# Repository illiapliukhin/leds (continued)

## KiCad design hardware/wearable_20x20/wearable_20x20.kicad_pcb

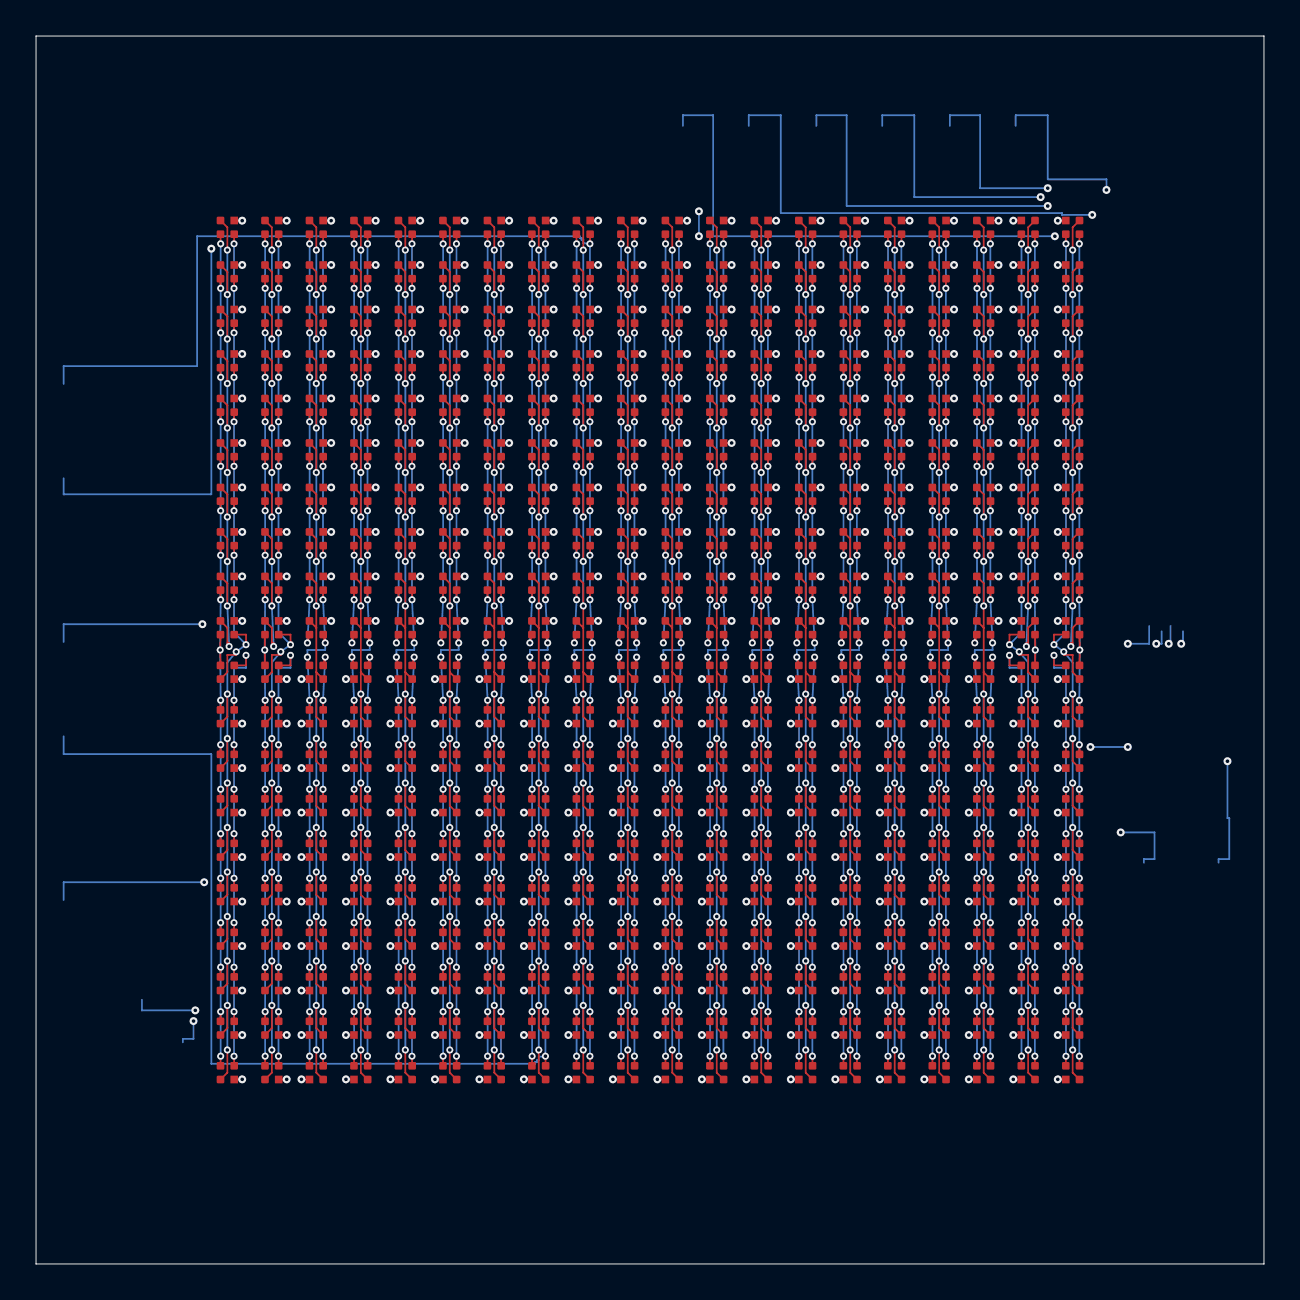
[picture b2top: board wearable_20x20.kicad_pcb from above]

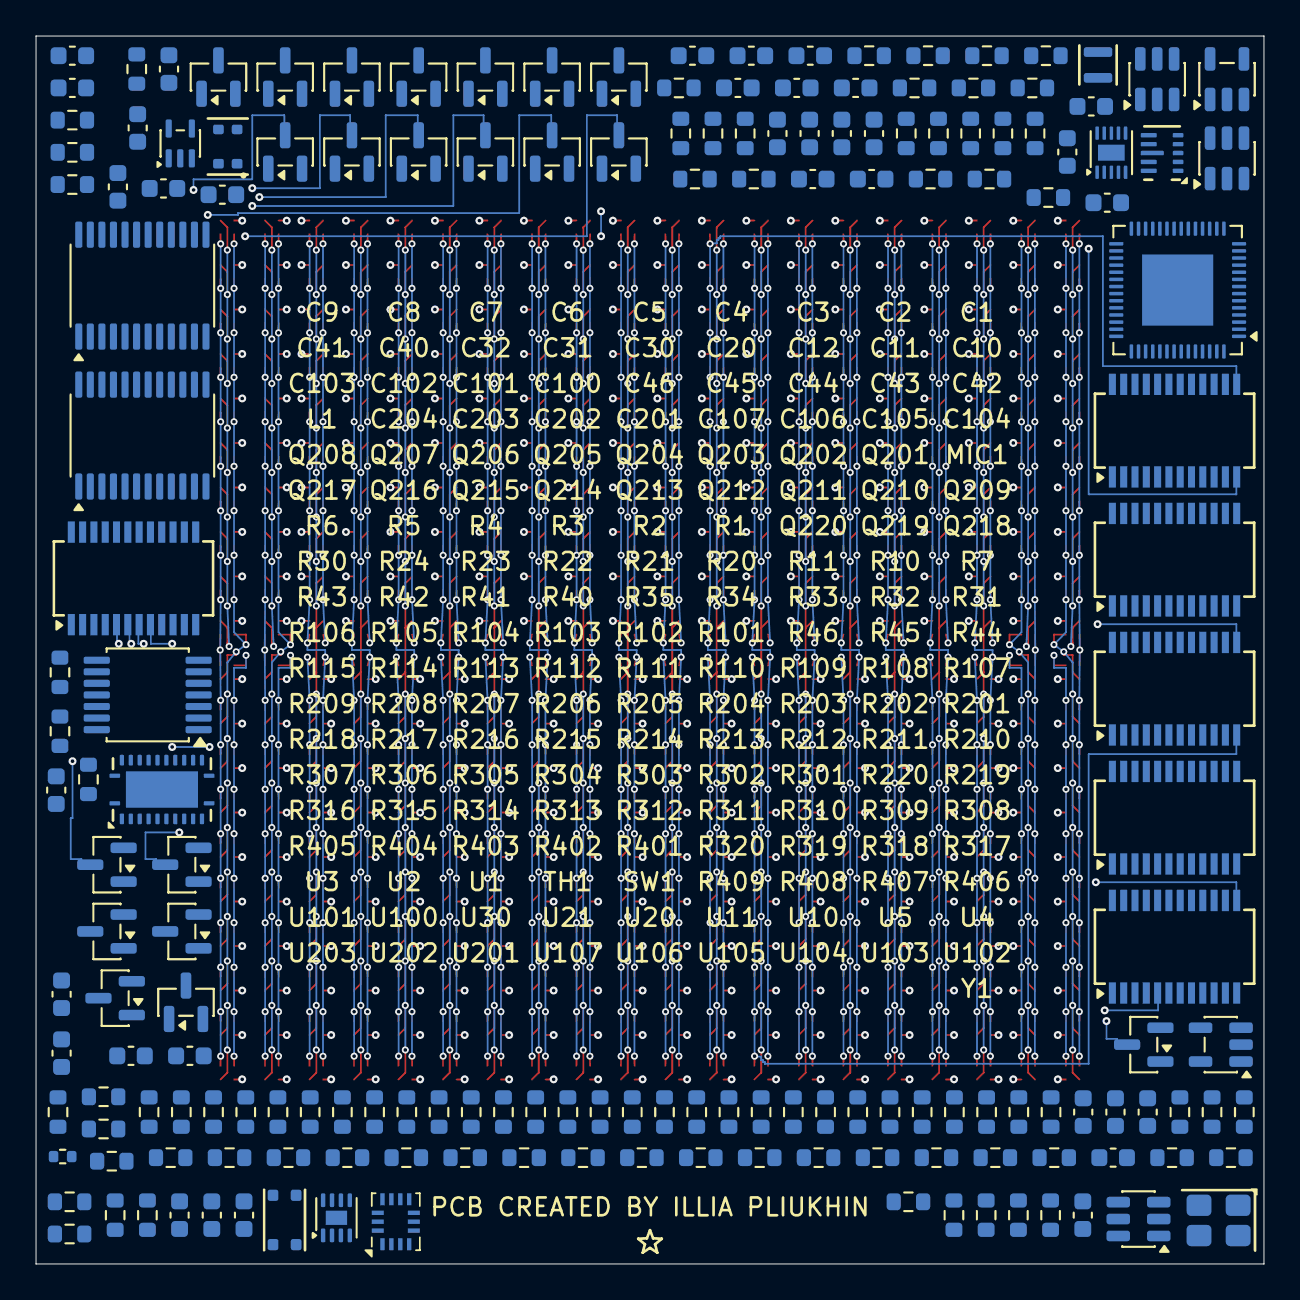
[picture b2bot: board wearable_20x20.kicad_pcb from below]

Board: 4 copper layers, 69.0 x 69.0 mm, 572 parts (172 on the bottom side), 205 nets.

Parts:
C1, C3, C4, C20, C40, C42: 1uF; C_0603_1608Metric
C2, C6, C10, C12: 10uF; C_0603_1608Metric
C5: 4.7uF; C_0603_1608Metric
C7, C8: 22uF; C_0603_1608Metric
C9, C11: 1nF; C_0603_1608Metric
C30, C32, C41, C43, C46, C100, C101, C102, C103, C104, C105, C106, C107, C201, C202, C203, C204: 100nF; C_0603_1608Metric
C31: 2.2uF; C_0603_1608Metric
C44: 100pF; C_0603_1608Metric
C45: 22nF; C_0603_1608Metric
D1, D2, D3, D4, D5, D6, D7, D8, D9, D10, D11, D12, D13, D14, D15, D16, D17, D18, D19, D20, D21, D22, D23, D24, D25, D26, D27, D28, D29, D30, D31, D32, D33, D34, D35, D36, D37, D38, D39, D40, D41, D42, D43, D44, D45, D46, D47, D48, D49, D50, D51, D52, D53, D54, D55, D56, D57, D58, D59, D60, D61, D62, D63, D64, D65, D66, D67, D68, D69, D70, D71, D72, D73, D74, D75, D76, D77, D78, D79, D80, D81, D82, D83, D84, D85, D86, D87, D88, D89, D90, D91, D92, D93, D94, D95, D96, D97, D98, D99, D100, D101, D102, D103, D104, D105, D106, D107, D108, D109, D110, D111, D112, D113, D114, D115, D116, D117, D118, D119, D120, D121, D122, D123, D124, D125, D126, D127, D128, D129, D130, D131, D132, D133, D134, D135, D136, D137, D138, D139, D140, D141, D142, D143, D144, D145, D146, D147, D148, D149, D150, D151, D152, D153, D154, D155, D156, D157, D158, D159, D160, D161, D162, D163, D164, D165, D166, D167, D168, D169, D170, D171, D172, D173, D174, D175, D176, D177, D178, D179, D180, D181, D182, D183, D184, D185, D186, D187, D188, D189, D190, D191, D192, D193, D194, D195, D196, D197, D198, D199, D200, D201, D202, D203, D204, D205, D206, D207, D208, D209, D210, D211, D212, D213, D214, D215, D216, D217, D218, D219, D220, D221, D222, D223, D224, D225, D226, D227, D228, D229, D230, D231, D232, D233, D234, D235, D236, D237, D238, D239, D240, D241, D242, D243, D244, D245, D246, D247, D248, D249, D250, D251, D252, D253, D254, D255, D256, D257, D258, D259, D260, D261, D262, D263, D264, D265, D266, D267, D268, D269, D270, D271, D272, D273, D274, D275, D276, D277, D278, D279, D280, D281, D282, D283, D284, D285, D286, D287, D288, D289, D290, D291, D292, D293, D294, D295, D296, D297, D298, D299, D300, D301, D302, D303, D304, D305, D306, D307, D308, D309, D310, D311, D312, D313, D314, D315, D316, D317, D318, D319, D320, D321, D322, D323, D324, D325, D326, D327, D328, D329, D330, D331, D332, D333, D334, D335, D336, D337, D338, D339, D340, D341, D342, D343, D344, D345, D346, D347, D348, D349, D350, D351, D352, D353, D354, D355, D356, D357, D358, D359, D360, D361, D362, D363, D364, D365, D366, D367, D368, D369, D370, D371, D372, D373, D374, D375, D376, D377, D378, D379, D380, D381, D382, D383, D384, D385, D386, D387, D388, D389, D390, D391, D392, D393, D394, D395, D396, D397, D398, D399, D400: MHPA1010RGBDT
L1: DFE201612E-R47M=P2 0.47uH; Murata_DFE201612E_2.0x1.6mm
MIC1: NA-FFA381-A10-1; Gettop_NA-FFA381-A10-1_TopPort_Microphone
Q201, Q202, Q203, Q204, Q205, Q206, Q207, Q208, Q209, Q210, Q211, Q212, Q213, Q214, Q215, Q216, Q217, Q218, Q219, Q220: AO3403; SOT-23
R1: 24k; R_0603_1608Metric
R2, R7, R45: 1k; R_0603_1608Metric
R3: 655k 0.1%; R_0603_1608Metric
R4: 91k 0.1%; R_0603_1608Metric
R5, R6, R10, R32, R46, R107, R108, R109, R110, R402, R403, R404, R405: 100k; R_0603_1608Metric
R11: DNP; R_0603_1608Metric
R20, R33, R43, R401: 10k; R_0603_1608Metric
R21, R22, R113, R114, R115: 22R; R_0603_1608Metric
R23, R24: 5.1k; R_0603_1608Metric
R30, R31: 4.7k; R_0603_1608Metric
R34, R35, R408, R409: 0R; R_0603_1608Metric
R40: 100R; R_0603_1608Metric
R41, R42, R111, R112, R301, R302, R303, R304, R305, R306, R307, R308, R309, R310, R311, R312, R313, R314, R315, R316, R317, R318, R319, R320, R406, R407: 47k; R_0603_1608Metric
R44: 200k; R_0603_1608Metric
R101, R102, R103, R104, R105, R106: 1.96k 0.1%; R_0603_1608Metric
R201, R202, R203, R204, R205, R206, R207, R208, R209, R210, R211, R212, R213, R214, R215, R216, R217, R218, R219, R220: 33R; R_0603_1608Metric
SW1: EVPBL2A1F000; Panasonic_EVPBL2A1F000_Switch
TH1: TE 20021086-05 10k 1% B3435; R_0402_1005Metric
U1: BQ25185; Texas_DLH0010A_WSON-10-1EP_2.2x2mm_P0.4mm_EP0.9x1.5mm
U2: TPS7A2033PDBVR; SOT-23-5
U3: TPS63802DLAR; TI_DLA0010A_VSON-HR-10_2x3mm_P0.5mm
U4, U5: TPS22917DBVR; SOT-23-6
U10: ESP32-S3FN8; QFN-56-1EP_7x7mm_P0.4mm_EP4x4mm
U11: USBLC6-2SC6; SOT-23-6
U20: BMI270; Bosch_LGA-14_3x2.5mm_P0.5mm
U21: MAX17048G+T10; TDFN-8-1EP_2x2mm_P0.5mm_EP0.8x1.2mm
U30: TLV9001IDCKR; SOT-353_SC-70-5
U100: SN74LV125APWR; TSSOP-14_4.4x5mm_P0.65mm
U101, U102, U103, U104, U105, U106: MBI5124GP-B; SSOP-24_3.9x8.7mm_P0.635mm
U107: SN74LVC1G125DBVR; SOT-23-5
U201: SN74LVC8T245RHLR; TI_RHL0024A_VQFN-24-1EP_3.5x5.5mm_P0.5mm_EP2.05x4.05mm
U202, U203: 74HC154PW,118; TSSOP-24_4.4x7.8mm_P0.65mm
Y1: L327S400H11L 40MHz 10pF; Lucki_L327S400H11L_Crystal_3225-4Pin

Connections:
AON_3V3: C5.1, C30.1, C31.1, C201.1, R20.1, R30.1, R31.1, R32.2, R111.1, R401.2, U2.5, U4.1, U5.1, U10.2, U10.3, U10.20, U10.46, U10.55, U10.56, U20.5, U20.8, U20.10, U20.12, U201.1, U201.2
AUDIO_3V3: C12.1, C46.1, R40.2, R41.2, U5.6, U30.5
AUDIO_3V3_CT: C11.1, U5.4
AUDIO_3V3_QOD: R11.2, U5.5
AUDIO_EN: R10.2, U5.3, U10.42
BAT_RAW: C3.1, C32.1, U1.2, U21.2, U21.3
BMI_ASCX_UNUSED: R35.2, U20.3
BMI_ASDX_UNUSED: R34.2, U20.2
BUTTON_WAKE_N: R32.1, SW1.1, U10.16
CHG_CE_N: U1.4, U10.43
CHG_ILIM_SET: R1.2, U1.7
CHG_ISET: R2.2, U1.8
CHG_STAT1_N: U1.9, U10.44
CHG_STAT2_N: U1.3, U10.45
CHIP_PU: C20.1, R20.2, U10.4
COL_B_01: D1.4 (K_B), D21.4 (K_B), D41.4 (K_B), D61.4 (K_B), D81.4 (K_B), D101.4 (K_B), D121.4 (K_B), D141.4 (K_B), D161.4 (K_B), D181.4 (K_B), D201.4 (K_B), D221.4 (K_B), D241.4 (K_B), D261.4 (K_B), D281.4 (K_B), D301.4 (K_B), D321.4 (K_B), D341.4 (K_B), D361.4 (K_B), D381.4 (K_B), U105.5
COL_B_02: D2.4 (K_B), D22.4 (K_B), D42.4 (K_B), D62.4 (K_B), D82.4 (K_B), D102.4 (K_B), D122.4 (K_B), D142.4 (K_B), D162.4 (K_B), D182.4 (K_B), D202.4 (K_B), D222.4 (K_B), D242.4 (K_B), D262.4 (K_B), D282.4 (K_B), D302.4 (K_B), D322.4 (K_B), D342.4 (K_B), D362.4 (K_B), D382.4 (K_B), U105.6
COL_B_03: D3.4 (K_B), D23.4 (K_B), D43.4 (K_B), D63.4 (K_B), D83.4 (K_B), D103.4 (K_B), D123.4 (K_B), D143.4 (K_B), D163.4 (K_B), D183.4 (K_B), D203.4 (K_B), D223.4 (K_B), D243.4 (K_B), D263.4 (K_B), D283.4 (K_B), D303.4 (K_B), D323.4 (K_B), D343.4 (K_B), D363.4 (K_B), D383.4 (K_B), U105.7
COL_B_04: D4.4 (K_B), D24.4 (K_B), D44.4 (K_B), D64.4 (K_B), D84.4 (K_B), D104.4 (K_B), D124.4 (K_B), D144.4 (K_B), D164.4 (K_B), D184.4 (K_B), D204.4 (K_B), D224.4 (K_B), D244.4 (K_B), D264.4 (K_B), D284.4 (K_B), D304.4 (K_B), D324.4 (K_B), D344.4 (K_B), D364.4 (K_B), D384.4 (K_B), U105.8
COL_B_05: D5.4 (K_B), D25.4 (K_B), D45.4 (K_B), D65.4 (K_B), D85.4 (K_B), D105.4 (K_B), D125.4 (K_B), D145.4 (K_B), D165.4 (K_B), D185.4 (K_B), D205.4 (K_B), D225.4 (K_B), D245.4 (K_B), D265.4 (K_B), D285.4 (K_B), D305.4 (K_B), D325.4 (K_B), D345.4 (K_B), D365.4 (K_B), D385.4 (K_B), U105.9
COL_B_06: D6.4 (K_B), D26.4 (K_B), D46.4 (K_B), D66.4 (K_B), D86.4 (K_B), D106.4 (K_B), D126.4 (K_B), D146.4 (K_B), D166.4 (K_B), D186.4 (K_B), D206.4 (K_B), D226.4 (K_B), D246.4 (K_B), D266.4 (K_B), D286.4 (K_B), D306.4 (K_B), D326.4 (K_B), D346.4 (K_B), D366.4 (K_B), D386.4 (K_B), U105.10
COL_B_07: D7.4 (K_B), D27.4 (K_B), D47.4 (K_B), D67.4 (K_B), D87.4 (K_B), D107.4 (K_B), D127.4 (K_B), D147.4 (K_B), D167.4 (K_B), D187.4 (K_B), D207.4 (K_B), D227.4 (K_B), D247.4 (K_B), D267.4 (K_B), D287.4 (K_B), D307.4 (K_B), D327.4 (K_B), D347.4 (K_B), D367.4 (K_B), D387.4 (K_B), U105.11
COL_B_08: D8.4 (K_B), D28.4 (K_B), D48.4 (K_B), D68.4 (K_B), D88.4 (K_B), D108.4 (K_B), D128.4 (K_B), D148.4 (K_B), D168.4 (K_B), D188.4 (K_B), D208.4 (K_B), D228.4 (K_B), D248.4 (K_B), D268.4 (K_B), D288.4 (K_B), D308.4 (K_B), D328.4 (K_B), D348.4 (K_B), D368.4 (K_B), D388.4 (K_B), U105.12
COL_B_09: D9.4 (K_B), D29.4 (K_B), D49.4 (K_B), D69.4 (K_B), D89.4 (K_B), D109.4 (K_B), D129.4 (K_B), D149.4 (K_B), D169.4 (K_B), D189.4 (K_B), D209.4 (K_B), D229.4 (K_B), D249.4 (K_B), D269.4 (K_B), D289.4 (K_B), D309.4 (K_B), D329.4 (K_B), D349.4 (K_B), D369.4 (K_B), D389.4 (K_B), U105.13
COL_B_10: D10.4 (K_B), D30.4 (K_B), D50.4 (K_B), D70.4 (K_B), D90.4 (K_B), D110.4 (K_B), D130.4 (K_B), D150.4 (K_B), D170.4 (K_B), D190.4 (K_B), D210.4 (K_B), D230.4 (K_B), D250.4 (K_B), D270.4 (K_B), D290.4 (K_B), D310.4 (K_B), D330.4 (K_B), D350.4 (K_B), D370.4 (K_B), D390.4 (K_B), U105.14
COL_B_11: D11.4 (K_B), D31.4 (K_B), D51.4 (K_B), D71.4 (K_B), D91.4 (K_B), D111.4 (K_B), D131.4 (K_B), D151.4 (K_B), D171.4 (K_B), D191.4 (K_B), D211.4 (K_B), D231.4 (K_B), D251.4 (K_B), D271.4 (K_B), D291.4 (K_B), D311.4 (K_B), D331.4 (K_B), D351.4 (K_B), D371.4 (K_B), D391.4 (K_B), U105.15
COL_B_12: D12.4 (K_B), D32.4 (K_B), D52.4 (K_B), D72.4 (K_B), D92.4 (K_B), D112.4 (K_B), D132.4 (K_B), D152.4 (K_B), D172.4 (K_B), D192.4 (K_B), D212.4 (K_B), D232.4 (K_B), D252.4 (K_B), D272.4 (K_B), D292.4 (K_B), D312.4 (K_B), D332.4 (K_B), D352.4 (K_B), D372.4 (K_B), D392.4 (K_B), U105.16
COL_B_13: D13.4 (K_B), D33.4 (K_B), D53.4 (K_B), D73.4 (K_B), D93.4 (K_B), D113.4 (K_B), D133.4 (K_B), D153.4 (K_B), D173.4 (K_B), D193.4 (K_B), D213.4 (K_B), D233.4 (K_B), D253.4 (K_B), D273.4 (K_B), D293.4 (K_B), D313.4 (K_B), D333.4 (K_B), D353.4 (K_B), D373.4 (K_B), D393.4 (K_B), U105.17
COL_B_14: D14.4 (K_B), D34.4 (K_B), D54.4 (K_B), D74.4 (K_B), D94.4 (K_B), D114.4 (K_B), D134.4 (K_B), D154.4 (K_B), D174.4 (K_B), D194.4 (K_B), D214.4 (K_B), D234.4 (K_B), D254.4 (K_B), D274.4 (K_B), D294.4 (K_B), D314.4 (K_B), D334.4 (K_B), D354.4 (K_B), D374.4 (K_B), D394.4 (K_B), U105.18
COL_B_15: D15.4 (K_B), D35.4 (K_B), D55.4 (K_B), D75.4 (K_B), D95.4 (K_B), D115.4 (K_B), D135.4 (K_B), D155.4 (K_B), D175.4 (K_B), D195.4 (K_B), D215.4 (K_B), D235.4 (K_B), D255.4 (K_B), D275.4 (K_B), D295.4 (K_B), D315.4 (K_B), D335.4 (K_B), D355.4 (K_B), D375.4 (K_B), D395.4 (K_B), U105.19
COL_B_16: D16.4 (K_B), D36.4 (K_B), D56.4 (K_B), D76.4 (K_B), D96.4 (K_B), D116.4 (K_B), D136.4 (K_B), D156.4 (K_B), D176.4 (K_B), D196.4 (K_B), D216.4 (K_B), D236.4 (K_B), D256.4 (K_B), D276.4 (K_B), D296.4 (K_B), D316.4 (K_B), D336.4 (K_B), D356.4 (K_B), D376.4 (K_B), D396.4 (K_B), U105.20
COL_B_17: D17.4 (K_B), D37.4 (K_B), D57.4 (K_B), D77.4 (K_B), D97.4 (K_B), D117.4 (K_B), D137.4 (K_B), D157.4 (K_B), D177.4 (K_B), D197.4 (K_B), D217.4 (K_B), D237.4 (K_B), D257.4 (K_B), D277.4 (K_B), D297.4 (K_B), D317.4 (K_B), D337.4 (K_B), D357.4 (K_B), D377.4 (K_B), D397.4 (K_B), U106.5
COL_B_18: D18.4 (K_B), D38.4 (K_B), D58.4 (K_B), D78.4 (K_B), D98.4 (K_B), D118.4 (K_B), D138.4 (K_B), D158.4 (K_B), D178.4 (K_B), D198.4 (K_B), D218.4 (K_B), D238.4 (K_B), D258.4 (K_B), D278.4 (K_B), D298.4 (K_B), D318.4 (K_B), D338.4 (K_B), D358.4 (K_B), D378.4 (K_B), D398.4 (K_B), U106.6
COL_B_19: D19.4 (K_B), D39.4 (K_B), D59.4 (K_B), D79.4 (K_B), D99.4 (K_B), D119.4 (K_B), D139.4 (K_B), D159.4 (K_B), D179.4 (K_B), D199.4 (K_B), D219.4 (K_B), D239.4 (K_B), D259.4 (K_B), D279.4 (K_B), D299.4 (K_B), D319.4 (K_B), D339.4 (K_B), D359.4 (K_B), D379.4 (K_B), D399.4 (K_B), U106.7
COL_B_20: D20.4 (K_B), D40.4 (K_B), D60.4 (K_B), D80.4 (K_B), D100.4 (K_B), D120.4 (K_B), D140.4 (K_B), D160.4 (K_B), D180.4 (K_B), D200.4 (K_B), D220.4 (K_B), D240.4 (K_B), D260.4 (K_B), D280.4 (K_B), D300.4 (K_B), D320.4 (K_B), D340.4 (K_B), D360.4 (K_B), D380.4 (K_B), D400.4 (K_B), U106.8
COL_G_01: D1.3 (K_G), D21.3 (K_G), D41.3 (K_G), D61.3 (K_G), D81.3 (K_G), D101.3 (K_G), D121.3 (K_G), D141.3 (K_G), D161.3 (K_G), D181.3 (K_G), D201.3 (K_G), D221.3 (K_G), D241.3 (K_G), D261.3 (K_G), D281.3 (K_G), D301.3 (K_G), D321.3 (K_G), D341.3 (K_G), D361.3 (K_G), D381.3 (K_G), U103.5
COL_G_02: D2.3 (K_G), D22.3 (K_G), D42.3 (K_G), D62.3 (K_G), D82.3 (K_G), D102.3 (K_G), D122.3 (K_G), D142.3 (K_G), D162.3 (K_G), D182.3 (K_G), D202.3 (K_G), D222.3 (K_G), D242.3 (K_G), D262.3 (K_G), D282.3 (K_G), D302.3 (K_G), D322.3 (K_G), D342.3 (K_G), D362.3 (K_G), D382.3 (K_G), U103.6
COL_G_03: D3.3 (K_G), D23.3 (K_G), D43.3 (K_G), D63.3 (K_G), D83.3 (K_G), D103.3 (K_G), D123.3 (K_G), D143.3 (K_G), D163.3 (K_G), D183.3 (K_G), D203.3 (K_G), D223.3 (K_G), D243.3 (K_G), D263.3 (K_G), D283.3 (K_G), D303.3 (K_G), D323.3 (K_G), D343.3 (K_G), D363.3 (K_G), D383.3 (K_G), U103.7
COL_G_04: D4.3 (K_G), D24.3 (K_G), D44.3 (K_G), D64.3 (K_G), D84.3 (K_G), D104.3 (K_G), D124.3 (K_G), D144.3 (K_G), D164.3 (K_G), D184.3 (K_G), D204.3 (K_G), D224.3 (K_G), D244.3 (K_G), D264.3 (K_G), D284.3 (K_G), D304.3 (K_G), D324.3 (K_G), D344.3 (K_G), D364.3 (K_G), D384.3 (K_G), U103.8
COL_G_05: D5.3 (K_G), D25.3 (K_G), D45.3 (K_G), D65.3 (K_G), D85.3 (K_G), D105.3 (K_G), D125.3 (K_G), D145.3 (K_G), D165.3 (K_G), D185.3 (K_G), D205.3 (K_G), D225.3 (K_G), D245.3 (K_G), D265.3 (K_G), D285.3 (K_G), D305.3 (K_G), D325.3 (K_G), D345.3 (K_G), D365.3 (K_G), D385.3 (K_G), U103.9
COL_G_06: D6.3 (K_G), D26.3 (K_G), D46.3 (K_G), D66.3 (K_G), D86.3 (K_G), D106.3 (K_G), D126.3 (K_G), D146.3 (K_G), D166.3 (K_G), D186.3 (K_G), D206.3 (K_G), D226.3 (K_G), D246.3 (K_G), D266.3 (K_G), D286.3 (K_G), D306.3 (K_G), D326.3 (K_G), D346.3 (K_G), D366.3 (K_G), D386.3 (K_G), U103.10
COL_G_07: D7.3 (K_G), D27.3 (K_G), D47.3 (K_G), D67.3 (K_G), D87.3 (K_G), D107.3 (K_G), D127.3 (K_G), D147.3 (K_G), D167.3 (K_G), D187.3 (K_G), D207.3 (K_G), D227.3 (K_G), D247.3 (K_G), D267.3 (K_G), D287.3 (K_G), D307.3 (K_G), D327.3 (K_G), D347.3 (K_G), D367.3 (K_G), D387.3 (K_G), U103.11
COL_G_08: D8.3 (K_G), D28.3 (K_G), D48.3 (K_G), D68.3 (K_G), D88.3 (K_G), D108.3 (K_G), D128.3 (K_G), D148.3 (K_G), D168.3 (K_G), D188.3 (K_G), D208.3 (K_G), D228.3 (K_G), D248.3 (K_G), D268.3 (K_G), D288.3 (K_G), D308.3 (K_G), D328.3 (K_G), D348.3 (K_G), D368.3 (K_G), D388.3 (K_G), U103.12
COL_G_09: D9.3 (K_G), D29.3 (K_G), D49.3 (K_G), D69.3 (K_G), D89.3 (K_G), D109.3 (K_G), D129.3 (K_G), D149.3 (K_G), D169.3 (K_G), D189.3 (K_G), D209.3 (K_G), D229.3 (K_G), D249.3 (K_G), D269.3 (K_G), D289.3 (K_G), D309.3 (K_G), D329.3 (K_G), D349.3 (K_G), D369.3 (K_G), D389.3 (K_G), U103.13
COL_G_10: D10.3 (K_G), D30.3 (K_G), D50.3 (K_G), D70.3 (K_G), D90.3 (K_G), D110.3 (K_G), D130.3 (K_G), D150.3 (K_G), D170.3 (K_G), D190.3 (K_G), D210.3 (K_G), D230.3 (K_G), D250.3 (K_G), D270.3 (K_G), D290.3 (K_G), D310.3 (K_G), D330.3 (K_G), D350.3 (K_G), D370.3 (K_G), D390.3 (K_G), U103.14
COL_G_11: D11.3 (K_G), D31.3 (K_G), D51.3 (K_G), D71.3 (K_G), D91.3 (K_G), D111.3 (K_G), D131.3 (K_G), D151.3 (K_G), D171.3 (K_G), D191.3 (K_G), D211.3 (K_G), D231.3 (K_G), D251.3 (K_G), D271.3 (K_G), D291.3 (K_G), D311.3 (K_G), D331.3 (K_G), D351.3 (K_G), D371.3 (K_G), D391.3 (K_G), U103.15
COL_G_12: D12.3 (K_G), D32.3 (K_G), D52.3 (K_G), D72.3 (K_G), D92.3 (K_G), D112.3 (K_G), D132.3 (K_G), D152.3 (K_G), D172.3 (K_G), D192.3 (K_G), D212.3 (K_G), D232.3 (K_G), D252.3 (K_G), D272.3 (K_G), D292.3 (K_G), D312.3 (K_G), D332.3 (K_G), D352.3 (K_G), D372.3 (K_G), D392.3 (K_G), U103.16
COL_G_13: D13.3 (K_G), D33.3 (K_G), D53.3 (K_G), D73.3 (K_G), D93.3 (K_G), D113.3 (K_G), D133.3 (K_G), D153.3 (K_G), D173.3 (K_G), D193.3 (K_G), D213.3 (K_G), D233.3 (K_G), D253.3 (K_G), D273.3 (K_G), D293.3 (K_G), D313.3 (K_G), D333.3 (K_G), D353.3 (K_G), D373.3 (K_G), D393.3 (K_G), U103.17
COL_G_14: D14.3 (K_G), D34.3 (K_G), D54.3 (K_G), D74.3 (K_G), D94.3 (K_G), D114.3 (K_G), D134.3 (K_G), D154.3 (K_G), D174.3 (K_G), D194.3 (K_G), D214.3 (K_G), D234.3 (K_G), D254.3 (K_G), D274.3 (K_G), D294.3 (K_G), D314.3 (K_G), D334.3 (K_G), D354.3 (K_G), D374.3 (K_G), D394.3 (K_G), U103.18
COL_G_15: D15.3 (K_G), D35.3 (K_G), D55.3 (K_G), D75.3 (K_G), D95.3 (K_G), D115.3 (K_G), D135.3 (K_G), D155.3 (K_G), D175.3 (K_G), D195.3 (K_G), D215.3 (K_G), D235.3 (K_G), D255.3 (K_G), D275.3 (K_G), D295.3 (K_G), D315.3 (K_G), D335.3 (K_G), D355.3 (K_G), D375.3 (K_G), D395.3 (K_G), U103.19
COL_G_16: D16.3 (K_G), D36.3 (K_G), D56.3 (K_G), D76.3 (K_G), D96.3 (K_G), D116.3 (K_G), D136.3 (K_G), D156.3 (K_G), D176.3 (K_G), D196.3 (K_G), D216.3 (K_G), D236.3 (K_G), D256.3 (K_G), D276.3 (K_G), D296.3 (K_G), D316.3 (K_G), D336.3 (K_G), D356.3 (K_G), D376.3 (K_G), D396.3 (K_G), U103.20
COL_G_17: D17.3 (K_G), D37.3 (K_G), D57.3 (K_G), D77.3 (K_G), D97.3 (K_G), D117.3 (K_G), D137.3 (K_G), D157.3 (K_G), D177.3 (K_G), D197.3 (K_G), D217.3 (K_G), D237.3 (K_G), D257.3 (K_G), D277.3 (K_G), D297.3 (K_G), D317.3 (K_G), D337.3 (K_G), D357.3 (K_G), D377.3 (K_G), D397.3 (K_G), U104.5
COL_G_18: D18.3 (K_G), D38.3 (K_G), D58.3 (K_G), D78.3 (K_G), D98.3 (K_G), D118.3 (K_G), D138.3 (K_G), D158.3 (K_G), D178.3 (K_G), D198.3 (K_G), D218.3 (K_G), D238.3 (K_G), D258.3 (K_G), D278.3 (K_G), D298.3 (K_G), D318.3 (K_G), D338.3 (K_G), D358.3 (K_G), D378.3 (K_G), D398.3 (K_G), U104.6
COL_G_19: D19.3 (K_G), D39.3 (K_G), D59.3 (K_G), D79.3 (K_G), D99.3 (K_G), D119.3 (K_G), D139.3 (K_G), D159.3 (K_G), D179.3 (K_G), D199.3 (K_G), D219.3 (K_G), D239.3 (K_G), D259.3 (K_G), D279.3 (K_G), D299.3 (K_G), D319.3 (K_G), D339.3 (K_G), D359.3 (K_G), D379.3 (K_G), D399.3 (K_G), U104.7
COL_G_20: D20.3 (K_G), D40.3 (K_G), D60.3 (K_G), D80.3 (K_G), D100.3 (K_G), D120.3 (K_G), D140.3 (K_G), D160.3 (K_G), D180.3 (K_G), D200.3 (K_G), D220.3 (K_G), D240.3 (K_G), D260.3 (K_G), D280.3 (K_G), D300.3 (K_G), D320.3 (K_G), D340.3 (K_G), D360.3 (K_G), D380.3 (K_G), D400.3 (K_G), U104.8
COL_R_01: D1.2 (K_R), D21.2 (K_R), D41.2 (K_R), D61.2 (K_R), D81.2 (K_R), D101.2 (K_R), D121.2 (K_R), D141.2 (K_R), D161.2 (K_R), D181.2 (K_R), D201.2 (K_R), D221.2 (K_R), D241.2 (K_R), D261.2 (K_R), D281.2 (K_R), D301.2 (K_R), D321.2 (K_R), D341.2 (K_R), D361.2 (K_R), D381.2 (K_R), U101.5
COL_R_02: D2.2 (K_R), D22.2 (K_R), D42.2 (K_R), D62.2 (K_R), D82.2 (K_R), D102.2 (K_R), D122.2 (K_R), D142.2 (K_R), D162.2 (K_R), D182.2 (K_R), D202.2 (K_R), D222.2 (K_R), D242.2 (K_R), D262.2 (K_R), D282.2 (K_R), D302.2 (K_R), D322.2 (K_R), D342.2 (K_R), D362.2 (K_R), D382.2 (K_R), U101.6
COL_R_03: D3.2 (K_R), D23.2 (K_R), D43.2 (K_R), D63.2 (K_R), D83.2 (K_R), D103.2 (K_R), D123.2 (K_R), D143.2 (K_R), D163.2 (K_R), D183.2 (K_R), D203.2 (K_R), D223.2 (K_R), D243.2 (K_R), D263.2 (K_R), D283.2 (K_R), D303.2 (K_R), D323.2 (K_R), D343.2 (K_R), D363.2 (K_R), D383.2 (K_R), U101.7
COL_R_04: D4.2 (K_R), D24.2 (K_R), D44.2 (K_R), D64.2 (K_R), D84.2 (K_R), D104.2 (K_R), D124.2 (K_R), D144.2 (K_R), D164.2 (K_R), D184.2 (K_R), D204.2 (K_R), D224.2 (K_R), D244.2 (K_R), D264.2 (K_R), D284.2 (K_R), D304.2 (K_R), D324.2 (K_R), D344.2 (K_R), D364.2 (K_R), D384.2 (K_R), U101.8
COL_R_05: D5.2 (K_R), D25.2 (K_R), D45.2 (K_R), D65.2 (K_R), D85.2 (K_R), D105.2 (K_R), D125.2 (K_R), D145.2 (K_R), D165.2 (K_R), D185.2 (K_R), D205.2 (K_R), D225.2 (K_R), D245.2 (K_R), D265.2 (K_R), D285.2 (K_R), D305.2 (K_R), D325.2 (K_R), D345.2 (K_R), D365.2 (K_R), D385.2 (K_R), U101.9
COL_R_06: D6.2 (K_R), D26.2 (K_R), D46.2 (K_R), D66.2 (K_R), D86.2 (K_R), D106.2 (K_R), D126.2 (K_R), D146.2 (K_R), D166.2 (K_R), D186.2 (K_R), D206.2 (K_R), D226.2 (K_R), D246.2 (K_R), D266.2 (K_R), D286.2 (K_R), D306.2 (K_R), D326.2 (K_R), D346.2 (K_R), D366.2 (K_R), D386.2 (K_R), U101.10
COL_R_07: D7.2 (K_R), D27.2 (K_R), D47.2 (K_R), D67.2 (K_R), D87.2 (K_R), D107.2 (K_R), D127.2 (K_R), D147.2 (K_R), D167.2 (K_R), D187.2 (K_R), D207.2 (K_R), D227.2 (K_R), D247.2 (K_R), D267.2 (K_R), D287.2 (K_R), D307.2 (K_R), D327.2 (K_R), D347.2 (K_R), D367.2 (K_R), D387.2 (K_R), U101.11
COL_R_08: D8.2 (K_R), D28.2 (K_R), D48.2 (K_R), D68.2 (K_R), D88.2 (K_R), D108.2 (K_R), D128.2 (K_R), D148.2 (K_R), D168.2 (K_R), D188.2 (K_R), D208.2 (K_R), D228.2 (K_R), D248.2 (K_R), D268.2 (K_R), D288.2 (K_R), D308.2 (K_R), D328.2 (K_R), D348.2 (K_R), D368.2 (K_R), D388.2 (K_R), U101.12
COL_R_09: D9.2 (K_R), D29.2 (K_R), D49.2 (K_R), D69.2 (K_R), D89.2 (K_R), D109.2 (K_R), D129.2 (K_R), D149.2 (K_R), D169.2 (K_R), D189.2 (K_R), D209.2 (K_R), D229.2 (K_R), D249.2 (K_R), D269.2 (K_R), D289.2 (K_R), D309.2 (K_R), D329.2 (K_R), D349.2 (K_R), D369.2 (K_R), D389.2 (K_R), U101.13
COL_R_10: D10.2 (K_R), D30.2 (K_R), D50.2 (K_R), D70.2 (K_R), D90.2 (K_R), D110.2 (K_R), D130.2 (K_R), D150.2 (K_R), D170.2 (K_R), D190.2 (K_R), D210.2 (K_R), D230.2 (K_R), D250.2 (K_R), D270.2 (K_R), D290.2 (K_R), D310.2 (K_R), D330.2 (K_R), D350.2 (K_R), D370.2 (K_R), D390.2 (K_R), U101.14
COL_R_11: D11.2 (K_R), D31.2 (K_R), D51.2 (K_R), D71.2 (K_R), D91.2 (K_R), D111.2 (K_R), D131.2 (K_R), D151.2 (K_R), D171.2 (K_R), D191.2 (K_R), D211.2 (K_R), D231.2 (K_R), D251.2 (K_R), D271.2 (K_R), D291.2 (K_R), D311.2 (K_R), D331.2 (K_R), D351.2 (K_R), D371.2 (K_R), D391.2 (K_R), U101.15
COL_R_12: D12.2 (K_R), D32.2 (K_R), D52.2 (K_R), D72.2 (K_R), D92.2 (K_R), D112.2 (K_R), D132.2 (K_R), D152.2 (K_R), D172.2 (K_R), D192.2 (K_R), D212.2 (K_R), D232.2 (K_R), D252.2 (K_R), D272.2 (K_R), D292.2 (K_R), D312.2 (K_R), D332.2 (K_R), D352.2 (K_R), D372.2 (K_R), D392.2 (K_R), U101.16
COL_R_13: D13.2 (K_R), D33.2 (K_R), D53.2 (K_R), D73.2 (K_R), D93.2 (K_R), D113.2 (K_R), D133.2 (K_R), D153.2 (K_R), D173.2 (K_R), D193.2 (K_R), D213.2 (K_R), D233.2 (K_R), D253.2 (K_R), D273.2 (K_R), D293.2 (K_R), D313.2 (K_R), D333.2 (K_R), D353.2 (K_R), D373.2 (K_R), D393.2 (K_R), U101.17
COL_R_14: D14.2 (K_R), D34.2 (K_R), D54.2 (K_R), D74.2 (K_R), D94.2 (K_R), D114.2 (K_R), D134.2 (K_R), D154.2 (K_R), D174.2 (K_R), D194.2 (K_R), D214.2 (K_R), D234.2 (K_R), D254.2 (K_R), D274.2 (K_R), D294.2 (K_R), D314.2 (K_R), D334.2 (K_R), D354.2 (K_R), D374.2 (K_R), D394.2 (K_R), U101.18
COL_R_15: D15.2 (K_R), D35.2 (K_R), D55.2 (K_R), D75.2 (K_R), D95.2 (K_R), D115.2 (K_R), D135.2 (K_R), D155.2 (K_R), D175.2 (K_R), D195.2 (K_R), D215.2 (K_R), D235.2 (K_R), D255.2 (K_R), D275.2 (K_R), D295.2 (K_R), D315.2 (K_R), D335.2 (K_R), D355.2 (K_R), D375.2 (K_R), D395.2 (K_R), U101.19
COL_R_16: D16.2 (K_R), D36.2 (K_R), D56.2 (K_R), D76.2 (K_R), D96.2 (K_R), D116.2 (K_R), D136.2 (K_R), D156.2 (K_R), D176.2 (K_R), D196.2 (K_R), D216.2 (K_R), D236.2 (K_R), D256.2 (K_R), D276.2 (K_R), D296.2 (K_R), D316.2 (K_R), D336.2 (K_R), D356.2 (K_R), D376.2 (K_R), D396.2 (K_R), U101.20
COL_R_17: D17.2 (K_R), D37.2 (K_R), D57.2 (K_R), D77.2 (K_R), D97.2 (K_R), D117.2 (K_R), D137.2 (K_R), D157.2 (K_R), D177.2 (K_R), D197.2 (K_R), D217.2 (K_R), D237.2 (K_R), D257.2 (K_R), D277.2 (K_R), D297.2 (K_R), D317.2 (K_R), D337.2 (K_R), D357.2 (K_R), D377.2 (K_R), D397.2 (K_R), U102.5
COL_R_18: D18.2 (K_R), D38.2 (K_R), D58.2 (K_R), D78.2 (K_R), D98.2 (K_R), D118.2 (K_R), D138.2 (K_R), D158.2 (K_R), D178.2 (K_R), D198.2 (K_R), D218.2 (K_R), D238.2 (K_R), D258.2 (K_R), D278.2 (K_R), D298.2 (K_R), D318.2 (K_R), D338.2 (K_R), D358.2 (K_R), D378.2 (K_R), D398.2 (K_R), U102.6
COL_R_19: D19.2 (K_R), D39.2 (K_R), D59.2 (K_R), D79.2 (K_R), D99.2 (K_R), D119.2 (K_R), D139.2 (K_R), D159.2 (K_R), D179.2 (K_R), D199.2 (K_R), D219.2 (K_R), D239.2 (K_R), D259.2 (K_R), D279.2 (K_R), D299.2 (K_R), D319.2 (K_R), D339.2 (K_R), D359.2 (K_R), D379.2 (K_R), D399.2 (K_R), U102.7
COL_R_20: D20.2 (K_R), D40.2 (K_R), D60.2 (K_R), D80.2 (K_R), D100.2 (K_R), D120.2 (K_R), D140.2 (K_R), D160.2 (K_R), D180.2 (K_R), D200.2 (K_R), D220.2 (K_R), D240.2 (K_R), D260.2 (K_R), D280.2 (K_R), D300.2 (K_R), D320.2 (K_R), D340.2 (K_R), D360.2 (K_R), D380.2 (K_R), D400.2 (K_R), U102.8
DEC_A_EN_4V1_N: R406.1, U201.17, U202.18
DEC_A_EN_N: U10.39, U201.7
DEC_B_EN_4V1_N: R407.1, U201.16, U203.18
DEC_B_EN_N: U10.40, U201.8
GAUGE_ALERT_N: U10.17, U21.5
GND: C1.2, C2.2, C3.2, C4.2, C5.2, C6.2, C7.2, C8.2, C9.2, C10.2, C11.2, C12.2, C20.2, C30.2, C31.2, C32.2, C40.2, C41.2, C43.2, C45.2, C46.2, C100.2, C101.2, C102.2, C103.2, C104.2, C105.2, C106.2, C107.2, C201.2, C202.2, C203.2, C204.2, MIC1.2, MIC1.3, R1.1, R2.1, R4.1, R5.1, R6.1, R7.1, R10.1, R11.1, R23.1, R24.1, R34.1, R35.1, R42.1, R101.1, R102.1, R103.1, R104.1, R105.1, R106.1, R107.2, R108.1, R109.1, R110.1, R402.2, R403.2, R404.2, R405.2, R408.2, R409.2, SW1.2, TH1.2, U1.5, U1.11, U2.2, U3.2, U3.3, U3.8, U4.2, U5.2, U10.57, U11.2, U20.1, U20.6, U20.7, U21.1, U21.4, U21.6, U21.9, U30.2, U100.1, U100.4, U100.7, U100.10, U100.13, U101.1, U102.1, U103.1, U104.1, U105.1, U106.1, U107.1, U107.3, U201.11, U201.12, U201.13, U202.12, U202.19, U203.12, U203.19, Y1.2, Y1.4
I2C_SCL: R31.2, U10.14, U20.13, U21.7
I2C_SDA: R30.2, U10.13, U20.14, U21.8
IMU_INT1: U10.15, U20.4
LED_4V1: C7.1, C8.1, C202.1, C203.1, C204.1, Q201.2, Q202.2, Q203.2, Q204.2, Q205.2, Q206.2, Q207.2, Q208.2, Q209.2, Q210.2, Q211.2, Q212.2, Q213.2, Q214.2, Q215.2, Q216.2, Q217.2, Q218.2, Q219.2, Q220.2, R3.2, R301.2, R302.2, R303.2, R304.2, R305.2, R306.2, R307.2, R308.2, R309.2, R310.2, R311.2, R312.2, R313.2, R314.2, R315.2, R316.2, R317.2, R318.2, R319.2, R320.2, R406.2, R407.2, U3.6, U201.23, U201.24, U202.24, U203.24
LED_CHAIN_01: U101.22, U102.2
LED_CHAIN_02: U102.22, U103.2
LED_CHAIN_03: U103.22, U104.2
LED_CHAIN_04: U104.22, U105.2
LED_CHAIN_05: U105.22, U106.2
LED_CLK: R113.1, U101.3, U102.3, U103.3, U104.3, U105.3, U106.3
LED_CLK_BUF: R113.2, U100.3
LED_EN: R5.2, U3.1, U10.41
LED_FB: R3.1, R4.2, U3.4
LED_LE: R115.1, U101.4, U102.4, U103.4, U104.4, U105.4, U106.4
LED_LE_BUF: R115.2, U100.8
LED_LOGIC_3V3: C10.1, C100.1, C101.1, C102.1, C103.1, C104.1, C105.1, C106.1, C107.1, R112.1, U4.6, U100.14, U101.24, U102.24, U103.24, U104.24, U105.24, U106.24, U107.5
LED_LOGIC_3V3_CT: C9.1, U4.4
LED_LOGIC_3V3_QOD: R7.2, U4.5
LED_LOGIC_EN: R6.2, U4.3, U10.48
LED_OE_N: R112.2, U100.11, U101.21, U102.21, U103.21, U104.21, U105.21, U106.21
LED_SDI: R114.1, U101.2
LED_SDI_BUF: R114.2, U100.6
LED_SDO_FINAL: U106.22, U107.2
LED_SDO_RETURN: R107.1, U10.36, U107.4
LED_SW1: L1.1, U3.9
LED_SW2: L1.2, U3.7
MCU_LED_CLK: R108.2, U10.18, U100.2
MCU_LED_LE: R110.2, U10.21, U100.9
MCU_LED_OE_N: R111.2, U10.22, U100.12
MCU_LED_SDI: R109.2, U10.19, U100.5
MIC_ADC: C45.1, R45.1, U10.6
MIC_AFE_FB: C44.2, R43.2, R44.1, U30.4
MIC_AFE_IN: C42.2, R46.2, U30.3
MIC_AFE_OUT: C44.1, R44.2, R45.2, U30.1
MIC_BIAS: C43.1, R41.1, R42.2, R43.1, R46.1
MIC_RAW: C42.1, MIC1.4
MIC_VDD: C40.1, C41.1, MIC1.1, R40.1
PCB_NTC_ADC: R33.1, TH1.1, U10.9
PCB_NTC_EXCITE: R33.2, U10.10
ROW_01_ANODE: D1.1 (A), D2.1 (A), D3.1 (A), D4.1 (A), D5.1 (A), D6.1 (A), D7.1 (A), D8.1 (A), D9.1 (A), D10.1 (A), D11.1 (A), D12.1 (A), D13.1 (A), D14.1 (A), D15.1 (A), D16.1 (A), D17.1 (A), D18.1 (A), D19.1 (A), D20.1 (A), Q201.3
ROW_01_GATE: Q201.1, R201.2, R301.1
ROW_02_ANODE: D21.1 (A), D22.1 (A), D23.1 (A), D24.1 (A), D25.1 (A), D26.1 (A), D27.1 (A), D28.1 (A), D29.1 (A), D30.1 (A), D31.1 (A), D32.1 (A), D33.1 (A), D34.1 (A), D35.1 (A), D36.1 (A), D37.1 (A), D38.1 (A), D39.1 (A), D40.1 (A), Q202.3
ROW_02_GATE: Q202.1, R202.2, R302.1
ROW_03_ANODE: D41.1 (A), D42.1 (A), D43.1 (A), D44.1 (A), D45.1 (A), D46.1 (A), D47.1 (A), D48.1 (A), D49.1 (A), D50.1 (A), D51.1 (A), D52.1 (A), D53.1 (A), D54.1 (A), D55.1 (A), D56.1 (A), D57.1 (A), D58.1 (A), D59.1 (A), D60.1 (A), Q203.3
ROW_03_GATE: Q203.1, R203.2, R303.1
ROW_04_ANODE: D61.1 (A), D62.1 (A), D63.1 (A), D64.1 (A), D65.1 (A), D66.1 (A), D67.1 (A), D68.1 (A), D69.1 (A), D70.1 (A), D71.1 (A), D72.1 (A), D73.1 (A), D74.1 (A), D75.1 (A), D76.1 (A), D77.1 (A), D78.1 (A), D79.1 (A), D80.1 (A), Q204.3
ROW_04_GATE: Q204.1, R204.2, R304.1
ROW_05_ANODE: D81.1 (A), D82.1 (A), D83.1 (A), D84.1 (A), D85.1 (A), D86.1 (A), D87.1 (A), D88.1 (A), D89.1 (A), D90.1 (A), D91.1 (A), D92.1 (A), D93.1 (A), D94.1 (A), D95.1 (A), D96.1 (A), D97.1 (A), D98.1 (A), D99.1 (A), D100.1 (A), Q205.3
ROW_05_GATE: Q205.1, R205.2, R305.1
ROW_06_ANODE: D101.1 (A), D102.1 (A), D103.1 (A), D104.1 (A), D105.1 (A), D106.1 (A), D107.1 (A), D108.1 (A), D109.1 (A), D110.1 (A), D111.1 (A), D112.1 (A), D113.1 (A), D114.1 (A), D115.1 (A), D116.1 (A), D117.1 (A), D118.1 (A), D119.1 (A), D120.1 (A), Q206.3
ROW_06_GATE: Q206.1, R206.2, R306.1
ROW_07_ANODE: D121.1 (A), D122.1 (A), D123.1 (A), D124.1 (A), D125.1 (A), D126.1 (A), D127.1 (A), D128.1 (A), D129.1 (A), D130.1 (A), D131.1 (A), D132.1 (A), D133.1 (A), D134.1 (A), D135.1 (A), D136.1 (A), D137.1 (A), D138.1 (A), D139.1 (A), D140.1 (A), Q207.3
ROW_07_GATE: Q207.1, R207.2, R307.1
ROW_08_ANODE: D141.1 (A), D142.1 (A), D143.1 (A), D144.1 (A), D145.1 (A), D146.1 (A), D147.1 (A), D148.1 (A), D149.1 (A), D150.1 (A), D151.1 (A), D152.1 (A), D153.1 (A), D154.1 (A), D155.1 (A), D156.1 (A), D157.1 (A), D158.1 (A), D159.1 (A), D160.1 (A), Q208.3
ROW_08_GATE: Q208.1, R208.2, R308.1
ROW_09_ANODE: D161.1 (A), D162.1 (A), D163.1 (A), D164.1 (A), D165.1 (A), D166.1 (A), D167.1 (A), D168.1 (A), D169.1 (A), D170.1 (A), D171.1 (A), D172.1 (A), D173.1 (A), D174.1 (A), D175.1 (A), D176.1 (A), D177.1 (A), D178.1 (A), D179.1 (A), D180.1 (A), Q209.3
ROW_09_GATE: Q209.1, R209.2, R309.1
ROW_10_ANODE: D181.1 (A), D182.1 (A), D183.1 (A), D184.1 (A), D185.1 (A), D186.1 (A), D187.1 (A), D188.1 (A), D189.1 (A), D190.1 (A), D191.1 (A), D192.1 (A), D193.1 (A), D194.1 (A), D195.1 (A), D196.1 (A), D197.1 (A), D198.1 (A), D199.1 (A), D200.1 (A), Q210.3
ROW_10_GATE: Q210.1, R210.2, R310.1
ROW_11_ANODE: D201.1 (A), D202.1 (A), D203.1 (A), D204.1 (A), D205.1 (A), D206.1 (A), D207.1 (A), D208.1 (A), D209.1 (A), D210.1 (A), D211.1 (A), D212.1 (A), D213.1 (A), D214.1 (A), D215.1 (A), D216.1 (A), D217.1 (A), D218.1 (A), D219.1 (A), D220.1 (A), Q211.3
ROW_11_GATE: Q211.1, R211.2, R311.1
ROW_12_ANODE: D221.1 (A), D222.1 (A), D223.1 (A), D224.1 (A), D225.1 (A), D226.1 (A), D227.1 (A), D228.1 (A), D229.1 (A), D230.1 (A), D231.1 (A), D232.1 (A), D233.1 (A), D234.1 (A), D235.1 (A), D236.1 (A), D237.1 (A), D238.1 (A), D239.1 (A), D240.1 (A), Q212.3
ROW_12_GATE: Q212.1, R212.2, R312.1
ROW_13_ANODE: D241.1 (A), D242.1 (A), D243.1 (A), D244.1 (A), D245.1 (A), D246.1 (A), D247.1 (A), D248.1 (A), D249.1 (A), D250.1 (A), D251.1 (A), D252.1 (A), D253.1 (A), D254.1 (A), D255.1 (A), D256.1 (A), D257.1 (A), D258.1 (A), D259.1 (A), D260.1 (A), Q213.3
ROW_13_GATE: Q213.1, R213.2, R313.1
ROW_14_ANODE: D261.1 (A), D262.1 (A), D263.1 (A), D264.1 (A), D265.1 (A), D266.1 (A), D267.1 (A), D268.1 (A), D269.1 (A), D270.1 (A), D271.1 (A), D272.1 (A), D273.1 (A), D274.1 (A), D275.1 (A), D276.1 (A), D277.1 (A), D278.1 (A), D279.1 (A), D280.1 (A), Q214.3
ROW_14_GATE: Q214.1, R214.2, R314.1
ROW_15_ANODE: D281.1 (A), D282.1 (A), D283.1 (A), D284.1 (A), D285.1 (A), D286.1 (A), D287.1 (A), D288.1 (A), D289.1 (A), D290.1 (A), D291.1 (A), D292.1 (A), D293.1 (A), D294.1 (A), D295.1 (A), D296.1 (A), D297.1 (A), D298.1 (A), D299.1 (A), D300.1 (A), Q215.3
ROW_15_GATE: Q215.1, R215.2, R315.1
ROW_16_ANODE: D301.1 (A), D302.1 (A), D303.1 (A), D304.1 (A), D305.1 (A), D306.1 (A), D307.1 (A), D308.1 (A), D309.1 (A), D310.1 (A), D311.1 (A), D312.1 (A), D313.1 (A), D314.1 (A), D315.1 (A), D316.1 (A), D317.1 (A), D318.1 (A), D319.1 (A), D320.1 (A), Q216.3
ROW_16_GATE: Q216.1, R216.2, R316.1
ROW_17_ANODE: D321.1 (A), D322.1 (A), D323.1 (A), D324.1 (A), D325.1 (A), D326.1 (A), D327.1 (A), D328.1 (A), D329.1 (A), D330.1 (A), D331.1 (A), D332.1 (A), D333.1 (A), D334.1 (A), D335.1 (A), D336.1 (A), D337.1 (A), D338.1 (A), D339.1 (A), D340.1 (A), Q217.3
ROW_17_GATE: Q217.1, R217.2, R317.1
ROW_18_ANODE: D341.1 (A), D342.1 (A), D343.1 (A), D344.1 (A), D345.1 (A), D346.1 (A), D347.1 (A), D348.1 (A), D349.1 (A), D350.1 (A), D351.1 (A), D352.1 (A), D353.1 (A), D354.1 (A), D355.1 (A), D356.1 (A), D357.1 (A), D358.1 (A), D359.1 (A), D360.1 (A), Q218.3
ROW_18_GATE: Q218.1, R218.2, R318.1
ROW_19_ANODE: D361.1 (A), D362.1 (A), D363.1 (A), D364.1 (A), D365.1 (A), D366.1 (A), D367.1 (A), D368.1 (A), D369.1 (A), D370.1 (A), D371.1 (A), D372.1 (A), D373.1 (A), D374.1 (A), D375.1 (A), D376.1 (A), D377.1 (A), D378.1 (A), D379.1 (A), D380.1 (A), Q219.3
ROW_19_GATE: Q219.1, R219.2, R319.1
ROW_20_ANODE: D381.1 (A), D382.1 (A), D383.1 (A), D384.1 (A), D385.1 (A), D386.1 (A), D387.1 (A), D388.1 (A), D389.1 (A), D390.1 (A), D391.1 (A), D392.1 (A), D393.1 (A), D394.1 (A), D395.1 (A), D396.1 (A), D397.1 (A), D398.1 (A), D399.1 (A), D400.1 (A), Q220.3
ROW_20_GATE: Q220.1, R220.2, R320.1
ROW_A0: U10.23, U201.3
ROW_A0_4V1: R402.1, U201.21, U202.23, U203.23
ROW_A1: U10.24, U201.4
ROW_A1_4V1: R403.1, U201.20, U202.22, U203.22
ROW_A2: U10.27, U201.5
ROW_A2_4V1: R404.1, U201.19, U202.21, U203.21
ROW_A3: U10.38, U201.6
ROW_A3_4V1: R405.1, U201.18, U202.20, U203.20
ROW_XLAT_A7_UNUSED: R408.1, U201.9
ROW_XLAT_A8_UNUSED: R409.1, U201.10
ROW_XLAT_OE_N: R401.1, U10.37, U201.22
SYS: C2.1, C4.1, C6.1, U1.1, U2.1, U2.3, U3.10
U202_Y00_N: R201.1, U202.1
U202_Y01_N: R202.1, U202.2
U202_Y02_N: R203.1, U202.3
U202_Y03_N: R204.1, U202.4
U202_Y04_N: R205.1, U202.5
U202_Y05_N: R206.1, U202.6
U202_Y06_N: R207.1, U202.7
U202_Y07_N: R208.1, U202.8
U202_Y08_N: R209.1, U202.9
U202_Y09_N: R210.1, U202.10
U202_Y10_N: R211.1, U202.11
U202_Y11_N: R212.1, U202.13
U202_Y12_N: R213.1, U202.14
U202_Y13_N: R214.1, U202.15
U202_Y14_N: R215.1, U202.16
U202_Y15_N: R216.1, U202.17
U203_Y00_N: R217.1, U203.1
U203_Y01_N: R218.1, U203.2
U203_Y02_N: R219.1, U203.3
U203_Y03_N: R220.1, U203.4
USB_CONN_D_N: R21.1, U11.1, U11.6
USB_CONN_D_P: R22.1, U11.3, U11.4
USB_MCU_D_N: R21.2, U10.25
USB_MCU_D_P: R22.2, U10.26
U_LED_B_A_R_EXT: R105.2, U105.23
U_LED_B_B_R_EXT: R106.2, U106.23
U_LED_G_A_R_EXT: R103.2, U103.23
U_LED_G_B_R_EXT: R104.2, U104.23
U_LED_R_A_R_EXT: R101.2, U101.23
U_LED_R_B_R_EXT: R102.2, U102.23
VBUS_USB: C1.1, U1.10, U11.5
XTAL_N: U10.53, Y1.3
XTAL_P: U10.54, Y1.1

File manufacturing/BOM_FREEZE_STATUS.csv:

Category,Manufacturer Part,Status,Release blocker,Required evidence
MCU,ESP32-S3FN8,CONDITIONAL,"Full pin/reset/ADC audit; production schematic incomplete","Root netlist review; reset and power-ramp EVT"
RGB LED,MHPA1010RGBDT,CONDITIONAL,"Binning and alternate not approved","Supplier bin quote; optical EVT; approved alternate"
LED driver,MBI5124GP-B,CONDITIONAL,"Lifecycle alternate and thermal headroom open","Stock/lifecycle review; hot VDS/current measurements"
Row translator,SN74LVC8T245RHLR,CONDITIONAL,"Power-ramp behavior requires EVT","RHL0024A footprint audit; ramp/back-power test"
Row decoder,"74HC154PW,118",CONDITIONAL,"Gate timing not measured","Stock review; decoder/PMOS waveform test"
Row PMOS,AO3403,CONDITIONAL,"Drop and switching not measured","Hot voltage-drop and dead-time measurements"
LED signal buffer,SN74LV125APWR,CONDITIONAL,"Power-up behavior not measured","Stock review; ramp/back-power test"
LED SDO return buffer,SN74LVC1G125DBVR,CONDITIONAL,"Power-up behavior not measured","Stock review; configuration readback test"
IMU,BMI270,CONDITIONAL,"Bosch LGA-14 footprint released; interrupt and low-power configuration open","Wake and false-wake EVT"
Charger,BQ25185,CONDITIONAL,"TI DLH0010A footprint released; TS network and thermal policy open","Charge/load/NTC thermal EVT"
LED DC/DC,TPS63802DLAR,CONDITIONAL,"TI DLA0010A footprint released; load-transient and enclosure thermal margin open","Complete power layout; transient and thermal EVT"
AON LDO,TPS7A2033,CONDITIONAL,"Peak load and capacitor margin open","Load budget; transient measurement"
Fuel gauge,MAX17048G+T10,CONDITIONAL,"Maxim 21-0168 / 90-0065 footprint released; alert and hibernate configuration open","SOC/runtime characterization"
Microphone,"MA-HFA381-H13-1AF; alternate NA-FFA381-A10-1",CONDITIONAL,"Alternate exact symbol and manufacturer land pattern are released; AFE gain/bias and acoustic compatibility remain open","Supplier quote; placement review; acoustic and noise EVT"
Audio op amp,TLV9001IDCKR,CONDITIONAL,"ADC swing/noise/startup open","Complete layout; audio-noise EVT"
USB ESD,USBLC6-2SC6,CONDITIONAL,"Placement and USB signal integrity open","Complete USB layout; enumeration and ESD pre-compliance"
Crystal,L327S400H11L,CONDITIONAL,"Exact 4-pin symbol and SMD3225-4P footprint released; load network and layout open","Complete layout; frequency/startup measurement"
USB-C connector,"HH 16P TYPE-C (Y385), C52209107",BLOCKED_EXTERNAL,"Enclosure cross-section not frozen","Supplier drawing; enclosure fit; mating-cycle requirement"
Battery connector,"Molex 504050-0391 / 504051-0301 / 504052-0098",CONDITIONAL,"EVT connector set selected; battery harness and wire exit are not confirmed","Battery supplier mating confirmation; pin order; polarity; wire gauge; bend envelope"
Battery,"20x20 candidate HiMAXBATT LP603040; 28x28 RFQ baseline Akyga LP604050 AKY0679",BLOCKED_EXTERNAL,"20x20 finished pack exceeds provisional keepout; 28x28 harness and exact-part UN38.3 are not acceptable/confirmed","Production-intent finished-pack drawings; Pico-Lock harness; NTC table; UN38.3 test summaries; samples"
Inductor,DFE201612E-R47M=P2,CONDITIONAL,"Manufacturer footprint released; ordering code stock/lifecycle open","Authorized distributor lifecycle and stock review"
Rear button,Panasonic EVPBL2A1F000,CONDITIONAL,"Manufacturer land pattern released; enclosure plunger and preload remain undefined","Placement review; rear-cover plunger tolerance stack"
Battery NTC,"10k B3435",BLOCKED_EXTERNAL,"Must match selected pack","Battery supplier resistance table"
PCB NTC,"TE Connectivity 20021086-05",CONDITIONAL,"Standard 0402 footprint assigned; physical thermal correlation remains open","Placement review; thermal correlation EVT"
LED logic load switch,TPS22917DBVR,CONDITIONAL,"Ramp and QOD behavior open","Complete schematic; ramp/back-power EVT"
Audio load switch,TPS22917DBVR,CONDITIONAL,"Ramp and QOD behavior open","Complete schematic; startup/noise EVT"
Front panel,TBD smoked PC,BLOCKED_EXTERNAL,"Transmission and material not selected","Nine-sample optical EVT"
Pixel grid,TBD black polymer,BLOCKED_EXTERNAL,"Geometry and process not selected","SLA optical EVT; production process quote"
PCB,Custom 4-layer,BLOCKED_DESIGN,"Backside placement and routing incomplete","Final DRC; stackup; supplier DFM approval"
